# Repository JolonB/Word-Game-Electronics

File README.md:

# Word-Game-Electronics

Electronics for the Word Game project.

Dimensions are based on a standard Scrabble board, because this is based on standard Scrabble (don't tell Hasbro/Mattel).

## Tiles

The game tiles represent different letters that can be used to spell words, including a blank space tile which can be used to represent any letter.
The value of each tile is determined by the resistor inside it which is read by an ADC in the quarter it is placed in.
The tiles also have a 2-terminal male connector for connecting to the board.

The size of a single tile is 0.75"x0.75" (19.05x19.05mm), but the internal circuit is smaller.

## Segments

The internal board is made up of nine segments.
These segments each manage a 5x5 section of the 15x15 board.

Each segment consists of a microcontroller with an ADC, some analog multiplexers, 25 LEDs, and 25 tile connection units.
Each unit is made up of a two-terminal female piece connector and an LED.

<!-- TBD: perhaps use a digital MUX to control MOSFET connections to each piece instead, depending on price -->

The entire board has dimensions of 15"x15" (38.1cm), but there is some small spacing between letters, although the width isn't documented anywhere.
I have seen 0.05" (1.27mm) being used in some projects, which would make the play space 11.95" (0.05\*14 + 0.75\*15). This leaves 1.455" as outer padding, although this dimension isn't too important for the electronics.

The segments are communicated with over I2C.
Using the general call address (0x00) allows all I2C devices to receive a broadcast.
The segments connect to the controller board over a 8 wire interface:
* 2x I2C (SDA + SCK)
* 1x device select / interrupt
* 2x power
* 3x ground

The device select pin works much like SPI's chip select pin, but only during provisioning.
This allows a single segment to interpret the message, despite all segment receiving it, which allows the controller to set the I2C addresses automatically.
Once the I2C address is set, the segment takes control of the pin and can use it to send interrupts to the controller.
This pin is pulled up and each side can only control the pin in open collector mode.

## Controller

The controller is the central device that handles all of the communication.
It has nine ports arranged in a 3x3 grid for connecting each of the segments too.
Connecting the segments correctly means it can automatically commission the boards to have the correct coordinates.

Besides these connections, this board will also display content on LCD screens and will have connections for buttons for each of the players to interact with.

The controller will communicate with the segments using some protocol.
I considered SPI, but the Raspberry Pi Pico SDK only supports blocking SPI reads and writes, which could lock up the program.
I also considered I2C, but that would require provisioning to set up the ID for each segment, which I would rather avoid.
The alternative would be to add a chip-select pin, like SPI, to select the I2C device and rather than using an address, just have a method for specifying whether the message can be responded to (personal) or not (broadcasted).
The same logic could be used for UART too, although UART isn't meant to have multiple slaves connected.

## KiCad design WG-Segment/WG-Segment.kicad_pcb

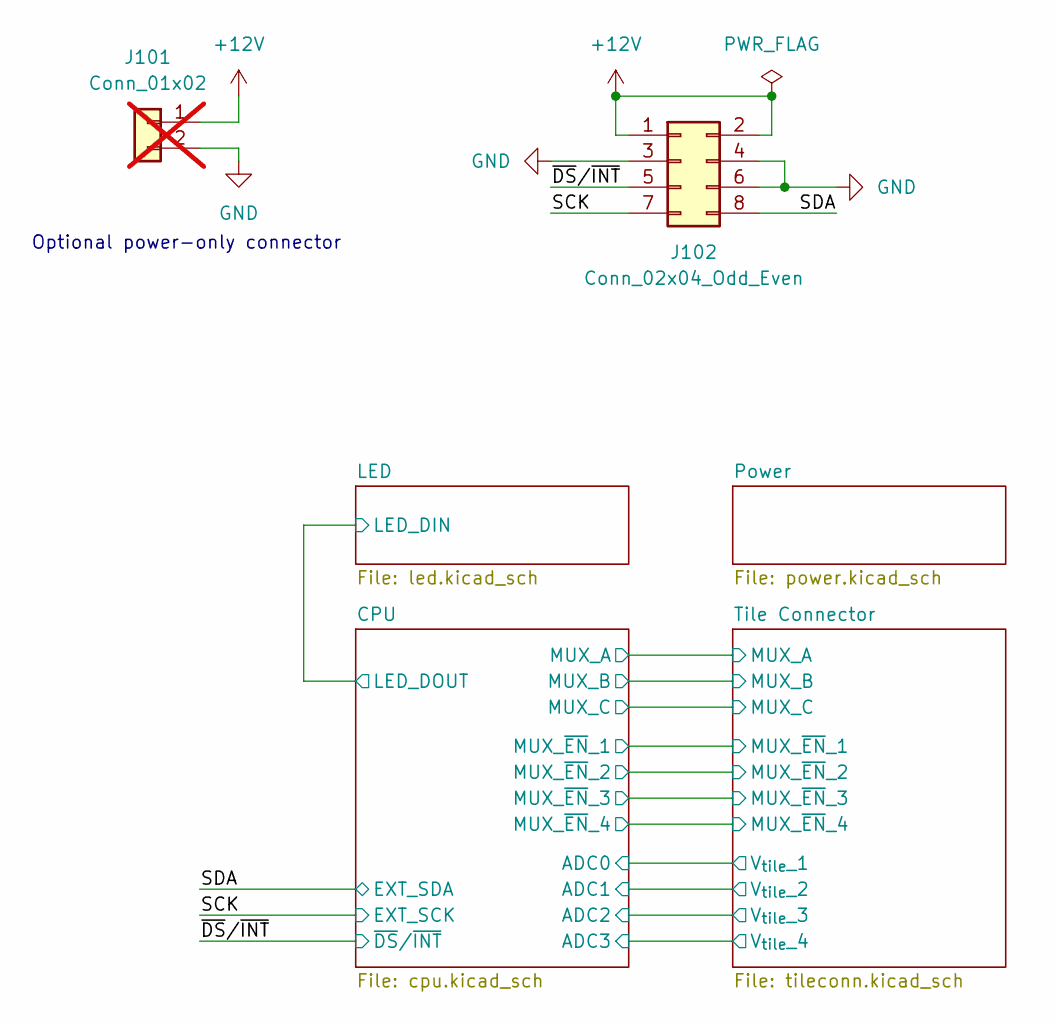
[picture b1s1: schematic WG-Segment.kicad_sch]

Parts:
J101: Conn_01x02; SolderWire-0.5sqmm_1x02_P4.6mm_D0.9mm_OD2.1mm; not fitted
J102: Conn_02x04_Odd_Even; IDC-Header_2x04_P2.54mm_Vertical

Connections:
+12V: J101.1, J102.1, J102.2; also elsewhere on the board
/SCK: J102.8; also elsewhere on the board
/SDA: J102.7; also elsewhere on the board

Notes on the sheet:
Optional power-only connector

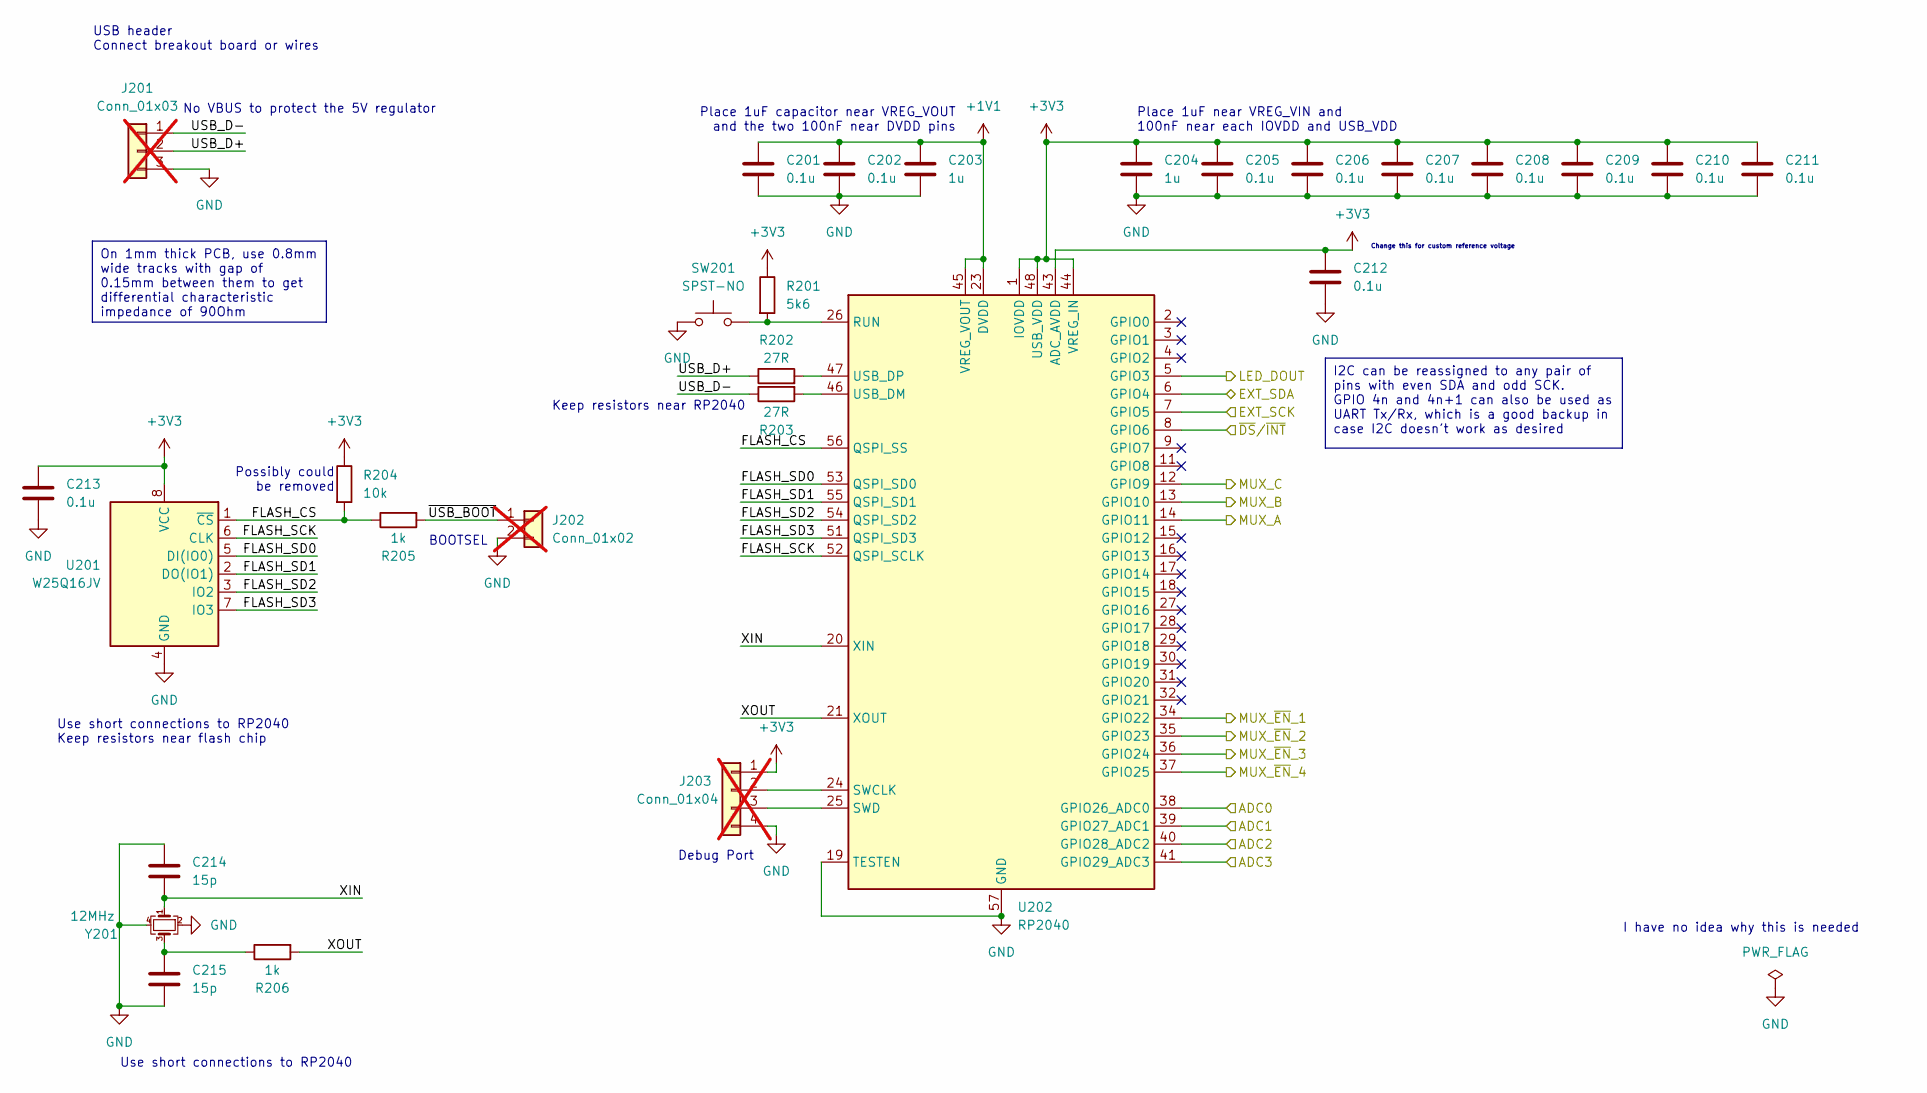
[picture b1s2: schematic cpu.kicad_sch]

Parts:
C201, C202, C205, C206, C207, C208, C209, C210, C211, C212, C213: 0.1u; C_0402_1005Metric_Pad0.74x0.62mm_HandSolder
C203, C204: 1u; C_0402_1005Metric_Pad0.74x0.62mm_HandSolder
C214, C215: 15p; C_0402_1005Metric_Pad0.74x0.62mm_HandSolder
J201: Conn_01x03; PinHeader_1x03_P2.54mm_Vertical; not fitted
J202: Conn_01x02; PinSocket_1x02_P2.54mm_Vertical; not fitted
J203: Conn_01x04; PinHeader_1x04_P2.54mm_Vertical; not fitted
R201: 5k6; R_0402_1005Metric_Pad0.72x0.64mm_HandSolder
R202, R203: 27R; R_0402_1005Metric_Pad0.72x0.64mm_HandSolder
R204: 10k; R_0402_1005Metric_Pad0.72x0.64mm_HandSolder
R205, R206: 1k; R_0402_1005Metric_Pad0.72x0.64mm_HandSolder
SW201: SPST-NO; SW_SPST_PTS810; Part Number PTS810SJK250SMTR LFS
U201: W25Q16JV; SOIC-8_5.23x5.23mm_P1.27mm; Part Number W25Q16JVSSIQ
U202: RP2040; QFN-56-1EP_7x7mm_P0.4mm_EP3.2x3.2mm; Part Number RP2040
Y201: 12MHz; Crystal_SMD_Abracon_ABM8G-4Pin_3.2x2.5mm; Part Number ABM8-272-T3

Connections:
+1V1: C201.1, C202.1, C203.1, U202.23 (DVDD), U202.45 (VREG_VOUT), U202.50 (DVDD)
+3V3: C204.1, C205.1, C206.1, C207.1, C208.1, C209.1, C210.1, C211.1, C212.1, C213.1, J203.1, R201.1, R204.1, U201.8 (VCC), U202.1 (IOVDD), U202.10 (IOVDD), U202.22 (IOVDD), U202.33 (IOVDD), U202.42 (IOVDD), U202.43 (ADC_AVDD), U202.44 (VREG_IN), U202.48 (USB_VDD), U202.49 (IOVDD); also elsewhere on the board
/CPU/ADC0: U202.38 (GPIO26_ADC0); also elsewhere on the board
/CPU/ADC1: U202.39 (GPIO27_ADC1); also elsewhere on the board
/CPU/ADC2: U202.40 (GPIO28_ADC2); also elsewhere on the board
/CPU/ADC3: U202.41 (GPIO29_ADC3); also elsewhere on the board
/CPU/FLASH_CS: R204.2, R205.1, U201.1 (~CS), U202.56 (QSPI_SS)
/CPU/FLASH_SCK: U201.6 (CLK), U202.52 (QSPI_SCLK)
/CPU/FLASH_SD0: U201.5 (DI(IO0)), U202.53 (QSPI_SD0)
/CPU/FLASH_SD1: U201.2 (DO(IO1)), U202.55 (QSPI_SD1)
/CPU/FLASH_SD2: U201.3 (IO2), U202.54 (QSPI_SD2)
/CPU/FLASH_SD3: U201.7 (IO3), U202.51 (QSPI_SD3)
/CPU/LED_DOUT: U202.5 (GPIO3); also elsewhere on the board
/CPU/MUX_A: U202.14 (GPIO11); also elsewhere on the board
/CPU/MUX_B: U202.13 (GPIO10); also elsewhere on the board
/CPU/MUX_C: U202.12 (GPIO9); also elsewhere on the board
/CPU/MUX_~EN_1: U202.34 (GPIO22); also elsewhere on the board
/CPU/MUX_~EN_2: U202.35 (GPIO23); also elsewhere on the board
/CPU/MUX_~EN_3: U202.36 (GPIO24); also elsewhere on the board
/CPU/MUX_~EN_4: U202.37 (GPIO25); also elsewhere on the board
/CPU/USB_D+: J201.2, R202.1
/CPU/USB_D-: J201.1, R203.1
/CPU/XIN: C214.2, U202.20 (XIN), Y201.1
/CPU/XOUT: R206.2, U202.21 (XOUT)
/CPU/~USB_BOOT: J202.1, R205.2
/SCK: U202.7 (GPIO5); also elsewhere on the board
/SDA: U202.6 (GPIO4); also elsewhere on the board
unnamed: C215.1, R206.1, Y201.3
unnamed: J203.2, U202.24 (SWCLK)
unnamed: J203.3, U202.25 (SWD)
unnamed: R201.2, SW201.2, U202.26 (RUN)
unnamed: R203.2, U202.46 (USB_DM)
unnamed: R202.2, U202.47 (USB_DP)

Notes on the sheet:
I2C can be reassigned to any pair of pins with even SDA and odd SCK. GPIO 4n and 4n+1 can also be used as UART Tx/Rx, which is a good backup in case I2C doesn't work as desired
On 1mm thick PCB, use 0.8mm wide tracks with gap of 0.15mm between them to get differential characteristic impedance of 90Ohm
USB header Connect breakout board or wires
I have no idea why this is needed
Keep resistors near RP2040
Debug Port
Use short connections to RP2040
No VBUS to protect the 5V regulator
Place 1uF near VREG_VIN and 100nF near each IOVDD and USB_VDD
Change this for custom reference voltage
Possibly could be removed
Use short connections to RP2040 Keep resistors near flash chip
Place 1uF capacitor near VREG_VOUT and the two 100nF near DVDD pins
BOOTSEL

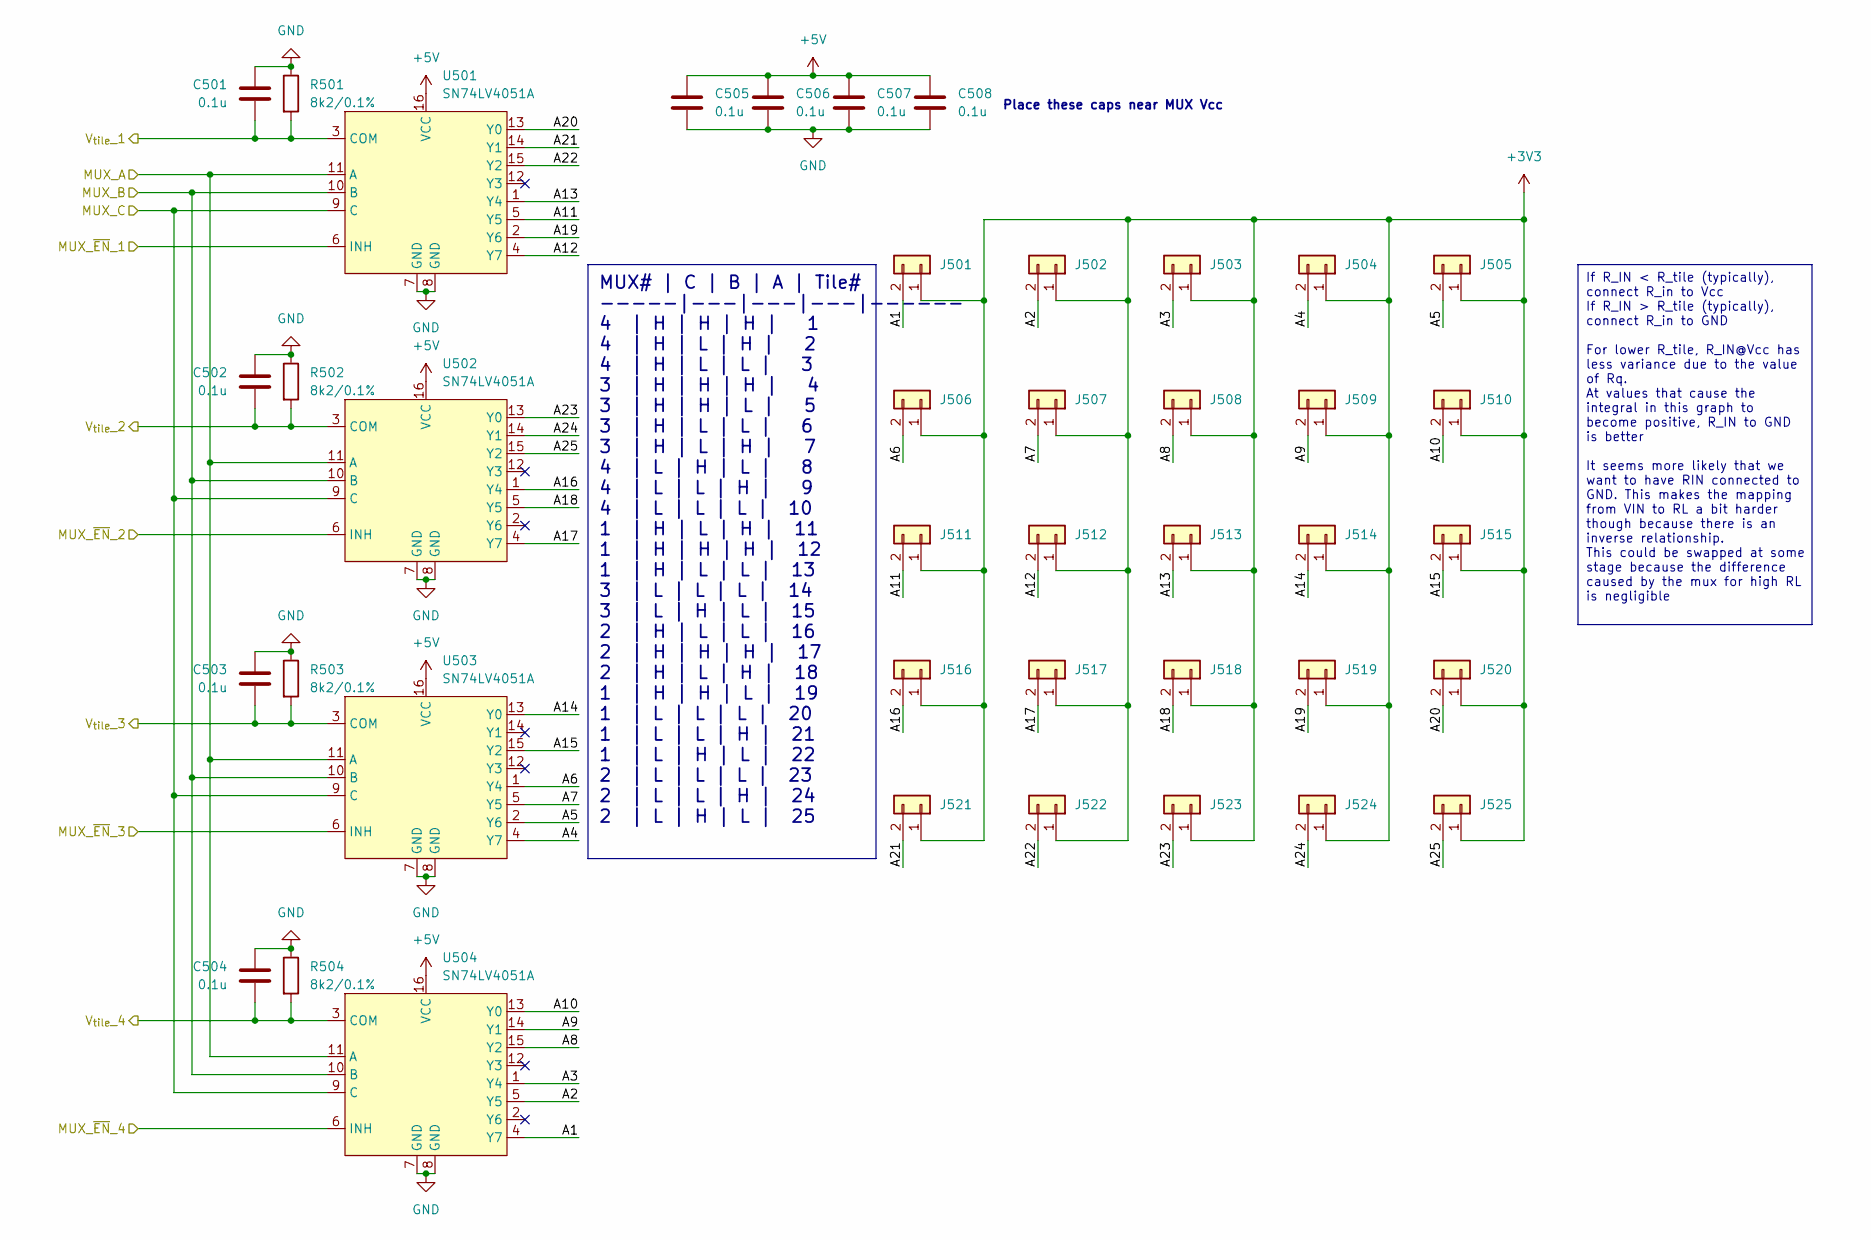
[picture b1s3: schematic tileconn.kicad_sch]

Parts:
C501, C502, C503, C504, C505, C506, C507, C508: 0.1u; C_0402_1005Metric_Pad0.74x0.62mm_HandSolder; LCSC Part C1525
J501, J502, J503, J504, J505, J506, J507, J508, J509, J510, J511, J512, J513, J514, J515, J516, J517, J518, J519, J520, J521, J522, J523, J524, J525: Conn_01x02; PinHeader_2x01_P1.00mm_Vertical
R501, R502, R503, R504: 8k2/0.1%; R_0402_1005Metric_Pad0.72x0.64mm_HandSolder; LCSC Part C25924
U501, U502, U503, U504: SN74LV4051A; TSSOP-16_4.4x5mm_P0.65mm; Part Number SN74LV4051APWR; LCSC Part C7793

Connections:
+3V3: J501.1, J502.1, J503.1, J504.1, J505.1, J506.1, J507.1, J508.1, J509.1, J510.1, J511.1, J512.1, J513.1, J514.1, J515.1, J516.1, J517.1, J518.1, J519.1, J520.1, J521.1, J522.1, J523.1, J524.1, J525.1; also elsewhere on the board
+5V: C505.1, C506.1, C507.1, C508.1, U501.16 (VCC), U502.16 (VCC), U503.16 (VCC), U504.16 (VCC); also elsewhere on the board
/CPU/ADC0: C501.1, R501.2, U501.3 (COM); also elsewhere on the board
/CPU/ADC1: C502.1, R502.2, U502.3 (COM); also elsewhere on the board
/CPU/ADC2: C503.1, R503.2, U503.3 (COM); also elsewhere on the board
/CPU/ADC3: C504.1, R504.2, U504.3 (COM); also elsewhere on the board
/CPU/MUX_A: U501.11 (A), U502.11 (A), U503.11 (A), U504.11 (A); also elsewhere on the board
/CPU/MUX_B: U501.10 (B), U502.10 (B), U503.10 (B), U504.10 (B); also elsewhere on the board
/CPU/MUX_C: U501.9 (C), U502.9 (C), U503.9 (C), U504.9 (C); also elsewhere on the board
/CPU/MUX_~EN_1: U501.6 (INH); also elsewhere on the board
/CPU/MUX_~EN_2: U502.6 (INH); also elsewhere on the board
/CPU/MUX_~EN_3: U503.6 (INH); also elsewhere on the board
/CPU/MUX_~EN_4: U504.6 (INH); also elsewhere on the board
/Tile Connector/A1: J501.2, U504.4 (Y7)
/Tile Connector/A2: J502.2, U504.5 (Y5)
/Tile Connector/A3: J503.2, U504.1 (Y4)
/Tile Connector/A4: J504.2, U503.4 (Y7)
/Tile Connector/A5: J505.2, U503.2 (Y6)
/Tile Connector/A6: J506.2, U503.1 (Y4)
/Tile Connector/A7: J507.2, U503.5 (Y5)
/Tile Connector/A8: J508.2, U504.15 (Y2)
/Tile Connector/A9: J509.2, U504.14 (Y1)
/Tile Connector/A10: J510.2, U504.13 (Y0)
/Tile Connector/A11: J511.2, U501.5 (Y5)
/Tile Connector/A12: J512.2, U501.4 (Y7)
/Tile Connector/A13: J513.2, U501.1 (Y4)
/Tile Connector/A14: J514.2, U503.13 (Y0)
/Tile Connector/A15: J515.2, U503.15 (Y2)
/Tile Connector/A16: J516.2, U502.1 (Y4)
/Tile Connector/A17: J517.2, U502.4 (Y7)
/Tile Connector/A18: J518.2, U502.5 (Y5)
/Tile Connector/A19: J519.2, U501.2 (Y6)
/Tile Connector/A20: J520.2, U501.13 (Y0)
/Tile Connector/A21: J521.2, U501.14 (Y1)
/Tile Connector/A22: J522.2, U501.15 (Y2)
/Tile Connector/A23: J523.2, U502.13 (Y0)
/Tile Connector/A24: J524.2, U502.14 (Y1)
/Tile Connector/A25: J525.2, U502.15 (Y2)

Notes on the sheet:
If R_IN < R_tile (typically), connect R_in to Vcc If R_IN > R_tile (typically), connect R_in to GND For lower R_tile, R_IN@Vcc has less variance due to the value of Rq. At values that cause the integral in this graph to become positive, R_IN to GND is better It seems more likely that we want to hav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
MUX# | C | B | A | Tile# -----|---|---|---|------ 4 | H | H | H | 1 4 | H | L | H | 2 4 | H | L | L | 3 3 | H | H | H | 4 3 | H | H | L | 5 3 | H | L | L | 6 3 | H | L | H | 7 4 | L | H | L | 8 4 | L | L | H | 9 4 | L | L | L | 10 1 | H | L | H | 11 1 | H | H | H | 12 1 | H | L | L | 13 3 | L | L |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
Place these caps near MUX Vcc

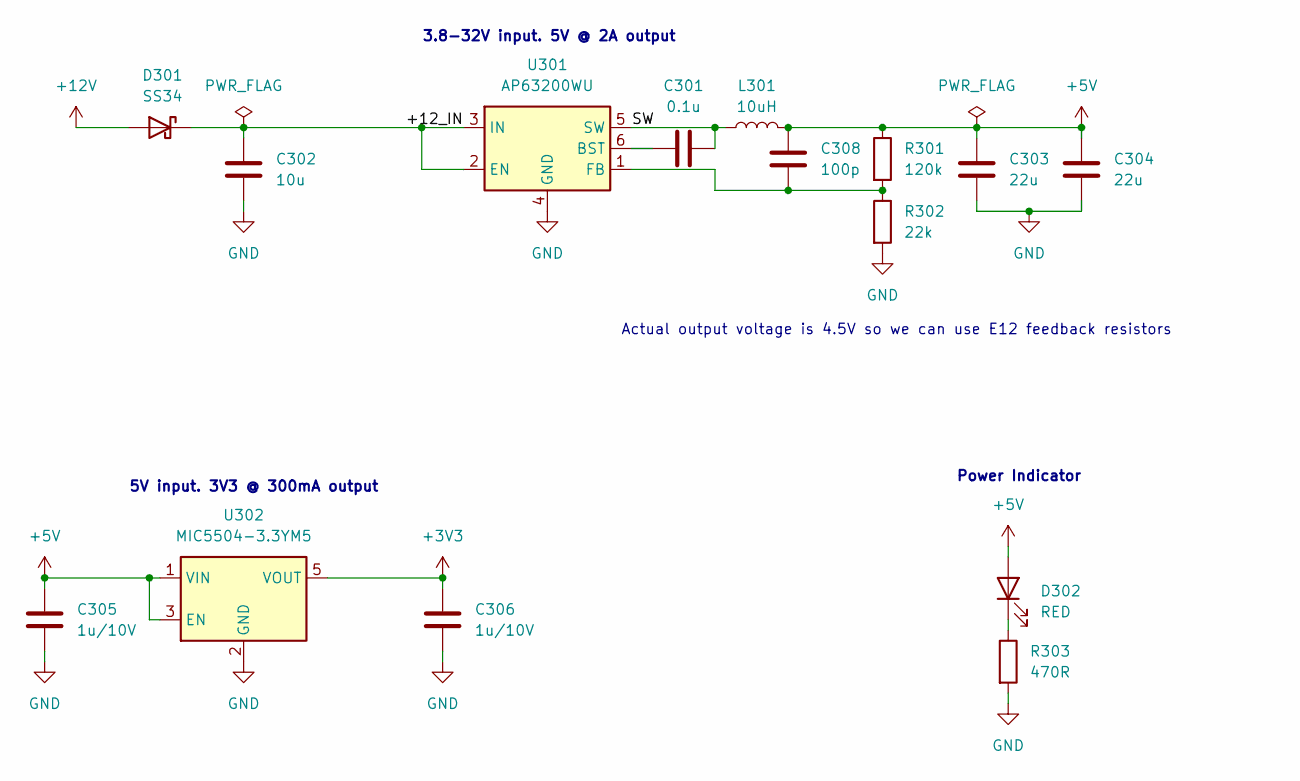
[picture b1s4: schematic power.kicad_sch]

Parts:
C301: 0.1u; C_0402_1005Metric_Pad0.74x0.62mm_HandSolder
C302: 10u; C_0805_2012Metric_Pad1.18x1.45mm_HandSolder; Part Number GRM21BR61E106KA73L
C303, C304: 22u; C_0805_2012Metric_Pad1.18x1.45mm_HandSolder; Part Number CL21A226MPQNNNE
C305, C306: 1u/10V; C_0402_1005Metric_Pad0.74x0.62mm_HandSolder; Part Number CL05A105KP5NNNC
C308: 100p; C_0402_1005Metric_Pad0.74x0.62mm_HandSolder
D301: SS34; D_SMA; Part Number SS34
D302: RED; LED_0603_1608Metric_Pad1.05x0.95mm_HandSolder; Part Number XL-1608SURC-06
L301: 10uH; Murata_6060; Part Number 1264EY-100M=P3
R301: 120k; R_0402_1005Metric_Pad0.72x0.64mm_HandSolder
R302: 22k; R_0402_1005Metric_Pad0.72x0.64mm_HandSolder
R303: 470R; R_0402_1005Metric_Pad0.72x0.64mm_HandSolder
U301: AP63200WU; TSOT-23-6; Part Number AP63200WU-7
U302: MIC5504-3.3YM5; SOT-23-5_HandSoldering; Part Number MIC5504-3.3YM5

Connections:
+3V3: C306.1, U302.5 (VOUT); also elsewhere on the board
+5V: C303.1, C304.1, C305.1, C308.1, D302.2 (A), L301.2, R301.1, U302.1 (VIN), U302.3 (EN); also elsewhere on the board
+12V: D301.2 (A); also elsewhere on the board
/Power/+12_IN: C302.1, D301.1 (K), U301.2 (EN), U301.3 (IN)
/Power/SW: C301.2, L301.1, U301.5 (SW)
unnamed: D302.1 (K), R303.1
unnamed: C301.1, U301.6 (BST)
unnamed 89: C308.2, R301.2, R302.1, U301.1 (FB); also elsewhere on the board

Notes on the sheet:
Actual output voltage is 4.5V so we can use E12 feedback resistors
3.8-32V input. 5V @ 2A output
Power Indicator
5V input. 3V3 @ 300mA output

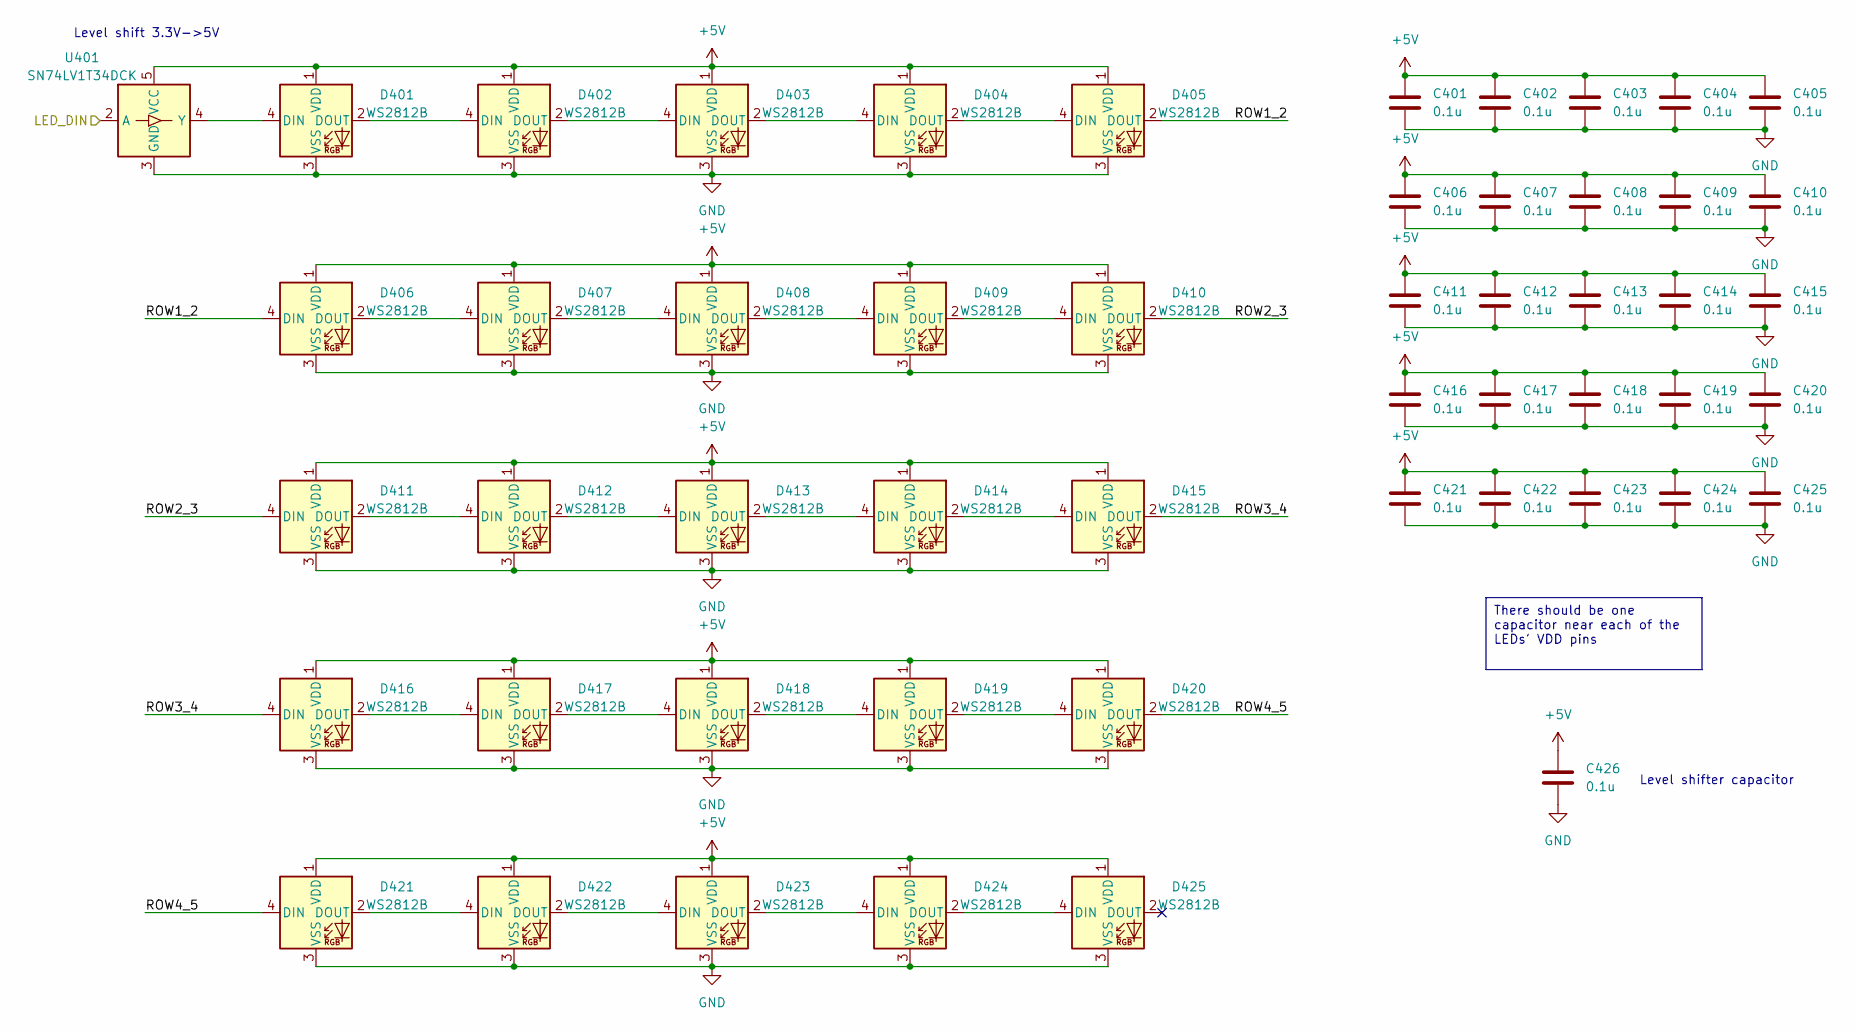
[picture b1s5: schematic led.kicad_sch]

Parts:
C401, C402, C403, C404, C405, C406, C407, C408, C409, C410, C411, C412, C413, C414, C415, C416, C417, C418, C419, C420, C421, C422, C423, C424, C425, C426: 0.1u; C_0402_1005Metric_Pad0.74x0.62mm_HandSolder
D401, D402, D403, D404, D405, D406, D407, D408, D409, D410, D411, D412, D413, D414, D415, D416, D417, D418, D419, D420, D421, D422, D423, D424, D425: WS2812B; LED_WS2812B_PLCC4_5.0x5.0mm_P3.2mm; Part Number WS2812B
U401: SN74LV1T34DCK; SOT-353_SC-70-5_Handsoldering; Part Number SN74LV1T34DCKR

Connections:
+5V: C401.1, C402.1, C403.1, C404.1, C405.1, C406.1, C407.1, C408.1, C409.1, C410.1, C411.1, C412.1, C413.1, C414.1, C415.1, C416.1, C417.1, C418.1, C419.1, C420.1, C421.1, C422.1, C423.1, C424.1, C425.1, C426.1, D401.1 (VDD), D402.1 (VDD), D403.1 (VDD), D404.1 (VDD), D405.1 (VDD), D406.1 (VDD), D407.1 (VDD), D408.1 (VDD), D409.1 (VDD), D410.1 (VDD), D411.1 (VDD), D412.1 (VDD), D413.1 (VDD), D414.1 (VDD), D415.1 (VDD), D416.1 (VDD), D417.1 (VDD), D418.1 (VDD), D419.1 (VDD), D420.1 (VDD), D421.1 (VDD), D422.1 (VDD), D423.1 (VDD), D424.1 (VDD), D425.1 (VDD), U401.5 (VCC); also elsewhere on the board
/CPU/LED_DOUT: U401.2 (A); also elsewhere on the board
/LED/ROW1_2: D405.2 (DOUT), D406.4 (DIN)
/LED/ROW2_3: D410.2 (DOUT), D411.4 (DIN)
/LED/ROW3_4: D415.2 (DOUT), D416.4 (DIN)
/LED/ROW4_5: D420.2 (DOUT), D421.4 (DIN)
unnamed: D401.4 (DIN), U401.4 (Y)
unnamed: D401.2 (DOUT), D402.4 (DIN)
unnamed: D402.2 (DOUT), D403.4 (DIN)
unnamed: D403.2 (DOUT), D404.4 (DIN)
unnamed: D404.2 (DOUT), D405.4 (DIN)
unnamed: D406.2 (DOUT), D407.4 (DIN)
unnamed: D407.2 (DOUT), D408.4 (DIN)
unnamed: D408.2 (DOUT), D409.4 (DIN)
unnamed: D409.2 (DOUT), D410.4 (DIN)
unnamed: D411.2 (DOUT), D412.4 (DIN)
unnamed: D412.2 (DOUT), D413.4 (DIN)
unnamed: D413.2 (DOUT), D414.4 (DIN)
unnamed: D414.2 (DOUT), D415.4 (DIN)
unnamed: D416.2 (DOUT), D417.4 (DIN)
unnamed: D417.2 (DOUT), D418.4 (DIN)
unnamed: D418.2 (DOUT), D419.4 (DIN)
unnamed: D419.2 (DOUT), D420.4 (DIN)
unnamed: D421.2 (DOUT), D422.4 (DIN)
unnamed: D422.2 (DOUT), D423.4 (DIN)
unnamed: D423.2 (DOUT), D424.4 (DIN)
unnamed: D424.2 (DOUT), D425.4 (DIN)

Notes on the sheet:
There should be one capacitor near each of the LEDs' VDD pins
Level shift 3.3V->5V
Level shifter capacitor

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
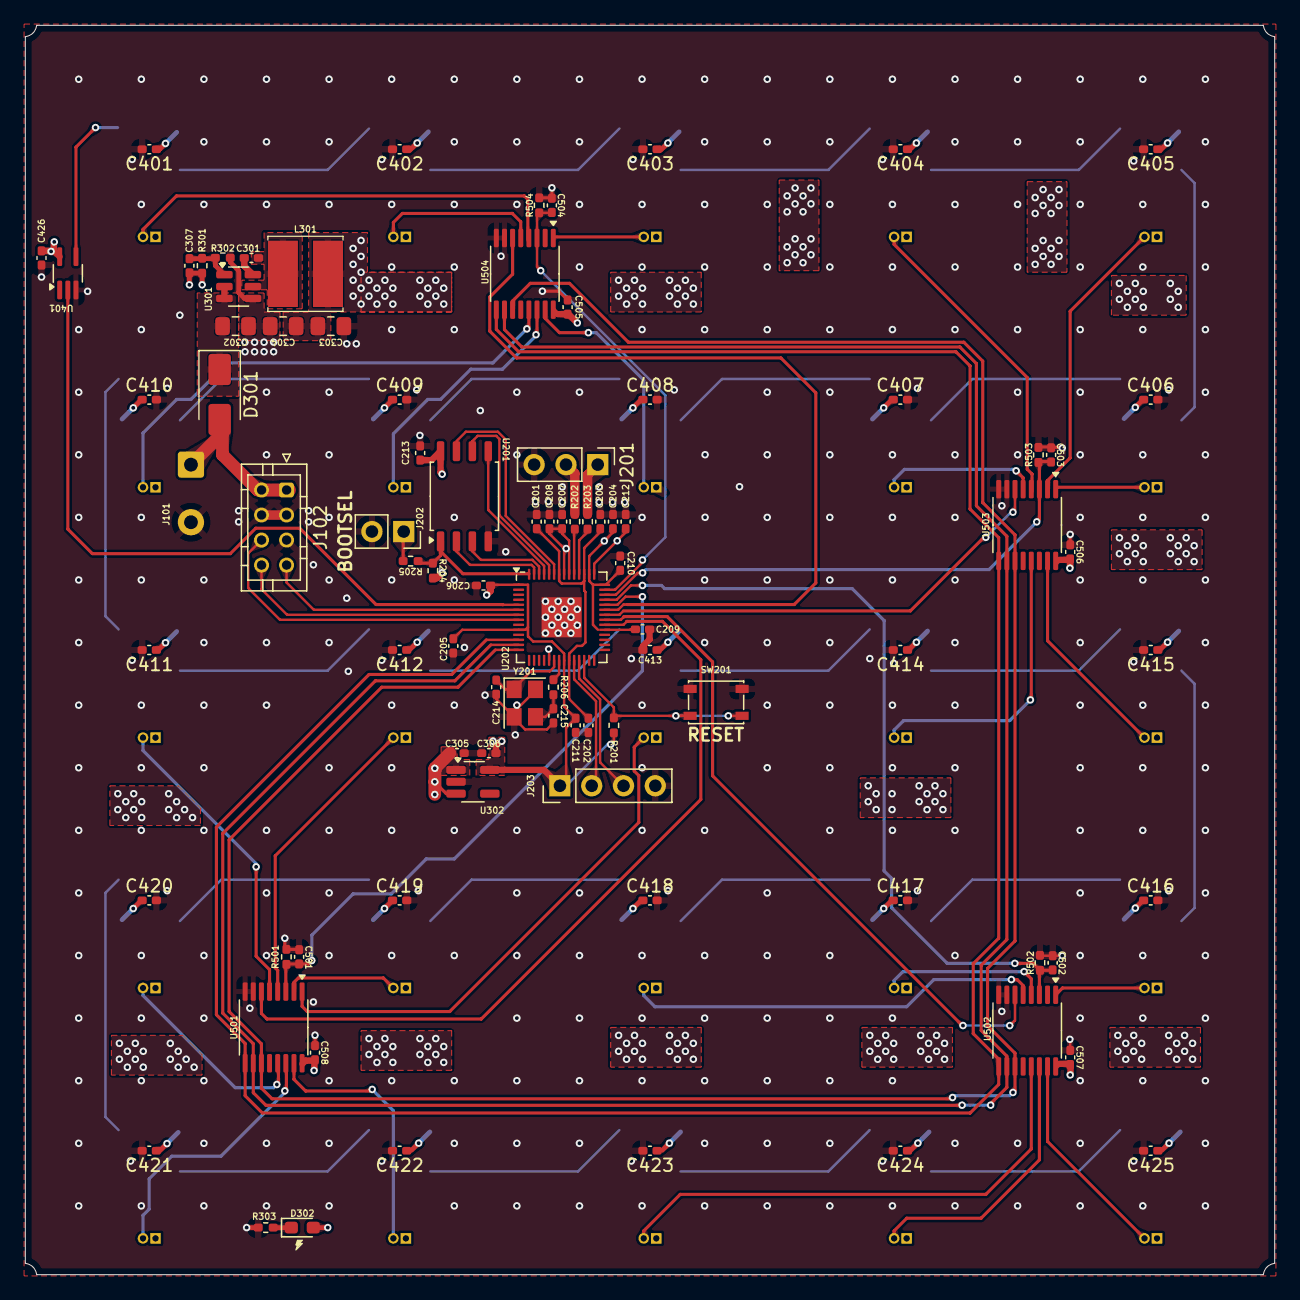
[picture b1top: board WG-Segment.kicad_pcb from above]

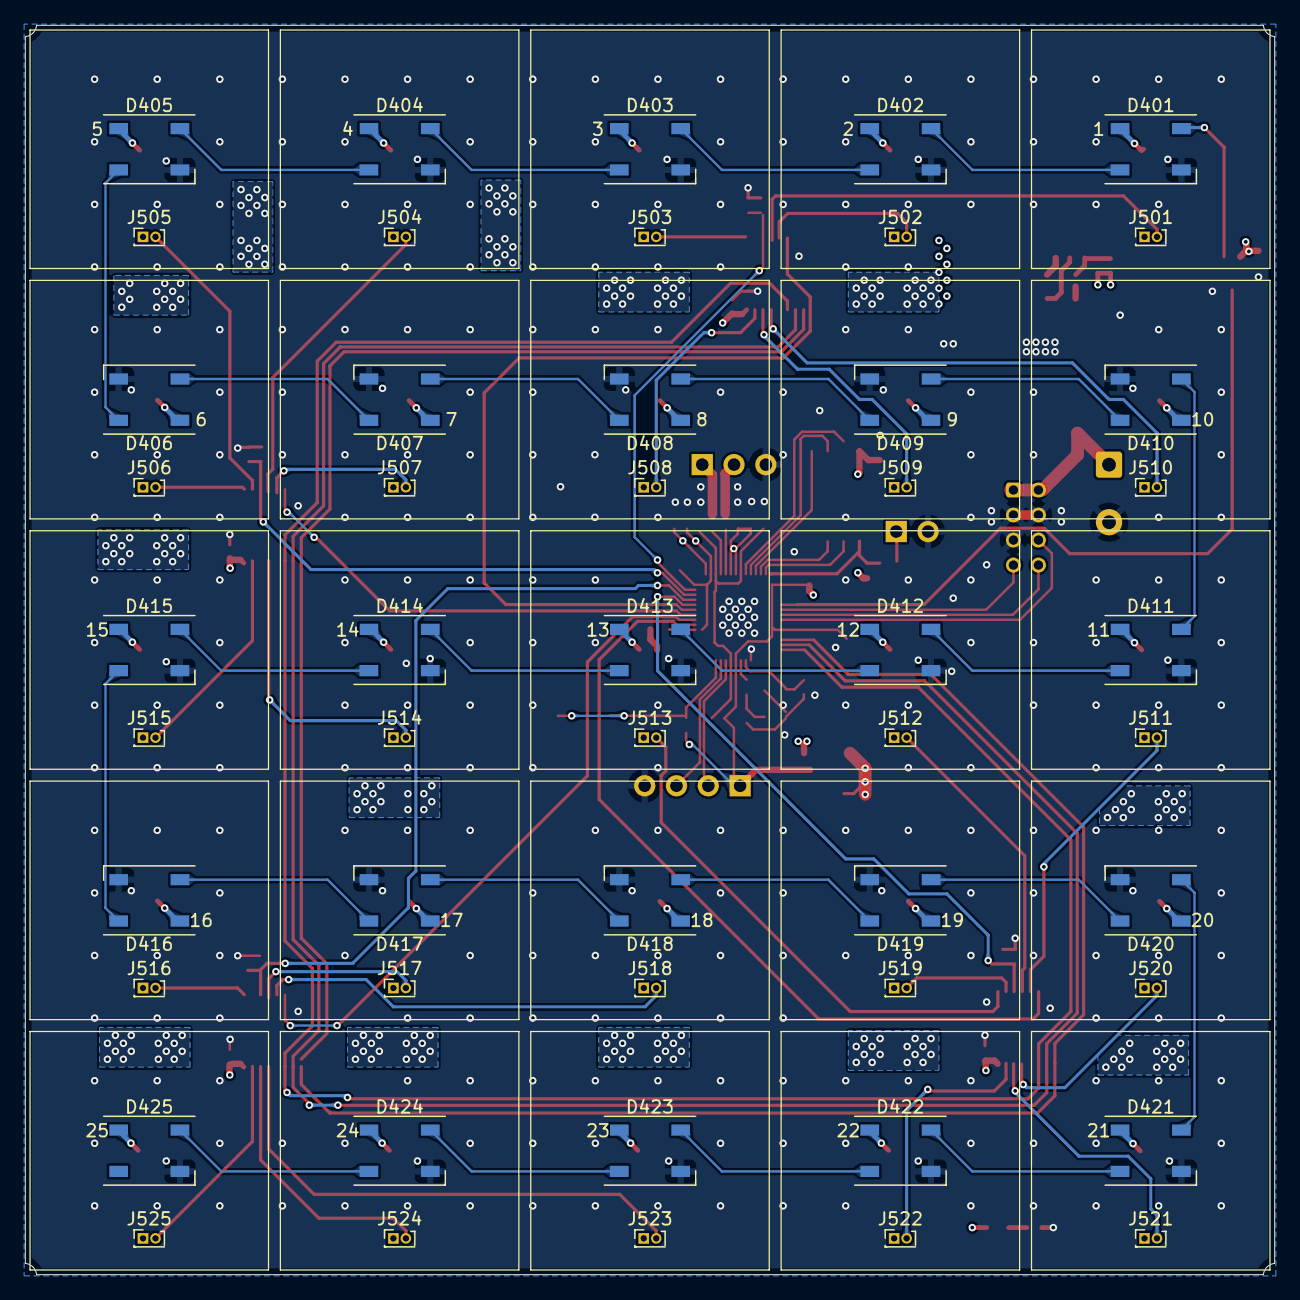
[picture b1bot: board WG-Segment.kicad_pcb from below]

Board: 4 copper layers, 99.8 x 99.8 mm, 138 parts (50 on the bottom side), 92 nets.

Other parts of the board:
C307: 100p; C_0402_1005Metric_Pad0.74x0.62mm_HandSolder

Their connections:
+5V: C307.1; also elsewhere on the board
unnamed 89: C307.2; also elsewhere on the board

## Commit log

2025-02-04 Add empty projects
2025-02-04 Create some of the segment piece
2025-02-09 Add symbol libraries
2025-02-09 Design full circuit
    Still need to run ERC
2025-02-10 Add level shifter to LED data input
2025-02-10 Set up PCB
2025-02-10 Update some stuff
2025-02-10 Add code example just so it is backed up
2025-02-11 Add 5x5 LED grid to PCB
2025-02-12 Position power circuitry
2025-02-16 Finish designing most of the PCB
    Only need to connect analog traces. May need to make the board a 4-layer PCB
2025-03-16 Add code samples
    Although I don't think any of these have the changes I want
2025-03-23 Add WG-Segment workflow
2025-03-23 Add missing kiplot config
2025-03-23 Allow tests to fail
    Only temporarily though
2025-03-23 Add microcontroller and connectors
2025-03-24 Add BOM and position files to workflow
2025-03-24 Move bom generation to sch
    Also reduce to kicad7
2025-03-24 Specify BOM columns
2025-03-25 Make position file match JLCPCB specs
2025-03-25 Fix id naming
2025-03-25 Fix DRC errors
2025-03-25 Change PCB to 4 layers
    Also fix all errors
2025-03-25 Update parts to ones in JLCPCB library
2025-03-25 Minor pinout adjustments
2025-03-25 Fix build issues
2025-03-25 Change component value
2025-03-25 Update gitignore
2025-03-25 Add tolerances and dimensions
2025-03-25 Update connector
2025-03-25 Add ADC-tile connections
2025-03-25 Update library paths to relative
2025-03-25 Remote TODO
2025-03-29 Update regulator
2025-03-30 Allow generating 4-layer PCBs
2025-03-31 Updates for smoother JLCPCB ordering
2025-03-31 Add LCSC part numbers
2025-06-25 Add tile implementation
2025-06-25 Update workflow
